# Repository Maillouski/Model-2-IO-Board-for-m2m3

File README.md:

# M2 IO Emulator Board

**English** | [Français](README.fr.md)

A drop-in replacement for the **Sega 837-10539 I/O board** of the **Daytona USA twin** cabinet (Sega Model 2), built around an
**Arduino Mega 2560**. It lets an emulator drive the original cabinet: controls, lamps, meters, the original drive board (force
feedback) and the original arcade monitor.

> **Status: prototype.** The design passes DRC and ERC, but no board has been built or tested yet. Read
> [Open points](#open-points) before you order.

**Version: V5.1** (2026-11-15). V5.1 adds a USB-A socket (J19) that carries only the cabinet's 5 V and ground (no data lines), for example to power a Raspberry Pi, and new silkscreen notes. V5 (kept under the tag [`v5`](https://github.com/Maillouski/Model-2-IO-Board-for-m2m3/tree/v5)) replaces the HDMI → VGA converter of V3 (CS5213, U4) with an **MS9292** (U9), adds a 3.3 V
regulator for it (U10), and adds two audio connectors (J17, J18). V3 added the [HDMI input](#hdmi-input), a stereo audio output
and a [composite sync](#composite-sync) that no longer depends on the polarity of H and V. The state before V5 (V3.2) is kept under the tag
[`v3.2`](https://github.com/Maillouski/Model-2-IO-Board-for-m2m3/tree/v3.2), V2 (screen jumper JP8) under the tag [`v2`](https://github.com/Maillouski/Model-2-IO-Board-for-m2m3/tree/v2), and V1,
the first board, ordered from JLCPCB on 2026-10-13, under the tag [`v1`](https://github.com/Maillouski/Model-2-IO-Board-for-m2m3/tree/v1).

## What it does

The idea is simple: pull the Sega I/O board out of the cabinet and put this one in its place. It has the same size, the same
mounting holes and the same connector names, so the original harness plugs straight in. Nothing gets cut or rewired.

Once it's in, the Arduino Mega becomes the bridge between the emulator and the cabinet. It reads the controls and drives
everything the original board used to drive:

- **Controls** — steering, accelerator, brake, shifter, coin, START, the VR view buttons, TEST and SERVICE.
- **Lamps, meters and relay** — switched by a ULN2803A, so the original bulbs and coin meters keep working.
- **Force feedback** — the original drive board stays in the cabinet and gets its commands from the Mega, so the wheel keeps
  its original force feedback.
- **Video** — an HDMI input (V3) or a VGA input goes to the original arcade monitor, with composite sync built on the board
  (negative, whatever the H/V polarity). A small switchable video amplifier lifts the signal to the level the tube expects.
- **Sound** — the audio carried by the HDMI input comes out on two RCA jacks (J16). A separate 3-pin input (J17) is passed straight
  through to a 4-pin output (J18) for the cabinet's preamp.
- **USB-A 5 V (J19)** — a USB-A socket wired to the cabinet's 5 V (+5V_BORNE) and ground only; D+ and D− are left unconnected, so it supplies power and no data. It is meant to power a small host such as a Raspberry Pi from the cabinet. Nothing protects it (no fuse). The silkscreen reminds you to set the cabinet's 5 V rail to 5.10 V.

A few practical details make bring-up easier: TEST and SERVICE buttons right on the board, a power LED, test points for each
supply, and a jumper (JP1) to choose whether the drive board logic runs from the Mega's 5 V or from the cabinet's.

## Video jumpers

| VIDEO IN (J13) | JP2-JP4 (VIDEO AMP) | JP5-JP7 (VGA TERM 75 Ω) |
|---|---|---|
| PC / HDMI-VGA adapter | ON | ON |
| Arcade RGB | OFF | OFF |

The same table is printed on the board. With the HDMI input, use the first row: U9 is the same kind of chip as the one inside an HDMI-to-VGA
adapter (V5.1 has not been built yet, see [Open points](#open-points)).

## Composite sync

U2 (74HCT86) builds the composite sync for the monitor from H and V, after the circuit of
[Tomi Engdahl](https://www.epanorama.net/circuits/vga2rgbs.html), pointed out by Zebidee on the ArcadeControls.com forum. Each sync is compared (XOR) with its own average, taken by an
RC filter (R66 + C47 for H, R67 + C48 for V: 2.2 kΩ, 22 µF), so its pulses always come out positive; the two are then combined
and inverted. The result is a **negative** composite sync whatever the polarity of H and V at the input, which is what the
original monitor expects. After a change of polarity (new video mode), the filters settle within a fraction of a second. It
goes to VIDEO OUT through R47 (470 Ω).

## HDMI input

J15 takes the host's HDMI output directly; U9 (Macrosilicon MS9292) turns it into analog R/G/B with H/V sync and stereo audio, so
no external HDMI → VGA adapter is needed. The VGA input J13 is still there, and a jumper chooses between the two. V3 used a CS5213
for this job; V5 uses the MS9292 because the CS5213 cannot be bought from regular distributors.

| Jumper | Setting | Effect |
|---|---|---|
| JP9 (VIDEO INPUT SOURCE) | ON | video from the HDMI input (J15, through U9) |
| JP9 | OFF | video from the VGA input (J13), as on V2 |
| JP10 (HDMI CHIP 5V SELECT) | 1-2 | U9 and its 3.3 V regulator run from the Mega's 5 V |
| JP10 | 2-3 | they run from the cabinet's 5 V, through a ferrite filter (FB1) |

- The switch is made by U7 (TS5V330, R/G/B) and U8 (74HCT157, H/V sync); everything after it (amplifier, composite sync, VIDEO
  OUT) is the same as on V2.
- **Power:** the MS9292 has no 5 V input pin. U10 (NCP1117ST33T3G) makes its 3.3 V from the 5 V of JP10; its 1.2 V comes from a
  buck converter inside the chip with L1 (10 µH power inductor, Bourns SRN4018-100M). Decoupling follows the maker's reference circuit (figure 3 of datasheet V1.5).
- **Video level:** the DAC outputs go to ground through R75-R77 (75 Ω), in parallel with the VGA termination R48-R50 (75 Ω, JP5-JP7), so
  the DAC sees 37.5 Ω. On an MS9292 evaluation board, 75 Ω alone made the video amplifier saturate.
- **Audio:** J16, a stacked RCA jack: **top = left**, **bottom = right**, fed by the chip's DAC through 470 Ω + 10 µF in series per
  channel. The footprint takes a Same Sky RCJ-2223 (DigiKey; red on top, so red = left) or a Lian Xin XDJK-0271-1650 (LCSC C7527522;
  white on top, red at the bottom). J17 (AUDIO input, 3-pin JST PH 2.00 mm: 1 left, 2 ground, 3 right) takes a straight cable from
  the host's line output and goes straight to J18 (AUDIO OUT, 4-pin JST NH 2.50 mm: 1 left, 2 ground, 3 right, 4 ground) for the
  cabinet's preamp. The two audio paths are separate: there is no selector.
- **Hot plug:** the chip drives the HPD line itself (its HDRXHPD output). The V3 pull-up R60 is not fitted.
- **EDID:** U6, an AT24C02 EEPROM on the HDMI DDC lines (address 0x50, decoupled by C24), is fitted and comes **blank**; U9's own
  DDC pins are not connected (R73 and R74, 0 Ω, are not fitted). The host must write a 256-byte EDID into it (the monitor's video mode, and HDMI audio if wanted):
  while it is blank, the host reads an invalid EDID. Its write protect is tied low, so it is programmed in place, through the
  HDMI cable.

## Screen jumper (JP8)

New in V2. JP8 ties the Mega's D36 pin to ground. The Mega reads it with its internal pull-up and sends it to the host with the
other inputs, so the host can choose its screen at start-up. Once the board is in the cabinet, switching screens only takes the
jumper, not a software change.

| JP8 | Screen |
|---|---|
| ON | CRT (4:3): the original arcade monitor, through the HDMI input (V3) or an HDMI-to-VGA adapter |
| OFF | LVDS panel (16:9) |

Printed on the board as SCREEN / ON = CRT (4:3) / OFF = LVDS 16:9. What the host does with this input is up to the host
software (see [Driving it from a computer](#driving-it-from-a-computer)).

## Driving it from a computer

The board comes with its Arduino Mega program ([`firmware/`](firmware/m2io-mega)) and a test console
([`tools/m2io_console.py`](tools/m2io_console.py)). To run Daytona USA on your own computer or emulator build and reach the
cabinet through this board, read **[Driving the board from your own host](docs/HOST-PROTOCOL.md)**: serial link, frames,
byte meanings, how to connect them to MAME's emulated I/O board, and the pitfalls to avoid.

## 3D views

Rendered with KiCad 10 from the files in this repository.

| | |
|---|---|
|  |  |
| Perspective view | Video section: VGA and HDMI inputs, source switch, OPA3355 amplifier, jumpers and settings tables |
|  |  |
| Top | Bottom |

## Repository

| Path | Contents |
|---|---|
| `kicad/` | KiCad 10 project: schematic, PCB, design rules, project footprint library (`interface-borne.pretty`), 3D models |
| `fabrication/` | Gerbers, Excellon drill files and drill maps (`gerbers/`), the same files zipped for the fab, pick-and-place file; JLCPCB BOM and CPL for SMD assembly ([`jlcpcb/`](fabrication/jlcpcb/README.md)) |
| `firmware/` | Arduino Mega program (`m2io-mega/`) and its PC test without a Mega (`test/`) |
| `tools/` | Test console: plays the host's part from any computer (Python 3 + pyserial) |
| `bom/` | Full BOM ([`BOM.md`](bom/BOM.md)) and DigiKey import file ([`BOM-digikey.csv`](bom/BOM-digikey.csv)) |
| `docs/` | [Host protocol](docs/HOST-PROTOCOL.md), schematic PDF, board renders |

Board: 2 layers, 180 × 190 mm. Gerbers come from the PCB's own plot settings (KiCad 10).

## Open points

- **V5.1 has not been built.** The MS9292 circuit follows the maker's reference design; the video levels were measured on an MS9292
  evaluation board, not on this board. Its behaviour with the 24 kHz mode of the arcade monitor on this board is not verified,
  and the HDMI pairs run on a 2-layer board without controlled impedance. V1 is the only board that has been ordered.
- **J19 (USB-A 5 V) is not verified under load.** The 5 V track that feeds it is 3 mm wide on most of its run, but the current it can deliver, the voltage drop and the need for a fuse have not been measured. The part is a Molex 67643-type USB-A socket (footprint and 3D model from the KiCad library); the exact part number is not confirmed, and it is not in the JLCPCB assembly files (solder it by hand).
- **U9's exposed pad is tied to ground**, which the datasheet does not state; check continuity (pad to pin 17) on the first chips. The pad
  has 9 vias: order "Epoxy Filled & Capped" vias or reduce the paste.
- **Fine vias and tracks:** the HDMI block uses 0.15 mm tracks and vias down to 0.45 / 0.20 mm (27 vias are 0.45 / 0.20 mm,
  right at the size JLCPCB surcharges); the rest of the board keeps 0.2 mm tracks and 0.6 / 0.3 mm vias. Confirm with the fabricator's quote.
- **CN1 and CN2** are plain 3M four-wall headers, without ejector latches.

## 3D models

The Arduino Mega model in `kicad/3d/` is derived from Arduino's CAD files (CC BY-SA 4.0) and KiCad library models; see
[`kicad/3d/README.md`](kicad/3d/README.md). The JST NH connectors and the RCA jack (J16, drawn as the RCJ-2223) use simplified models made for this project; U9, L1, U10 and J17 use the standard KiCad models.

## Credits

Sources used for this board: SEGA Daytona USA manuals; MAME (Dirk Best for the Model 1 I/O board; R. Belmont, O. Galibert,
ElSemi, A. Salese, M. Daniels for Model 2); M2Pac by BigPanik (Gamoover); DaytonaUSB by SailorSat; BackForceFeeder by njz3; MEGA
adapters by Tibal; the MiSTer project (video to arcade monitor); Tomi Engdahl (composite sync circuit); Zebidee on the ArcadeControls.com forum.

Not affiliated with or endorsed by SEGA.

## License

© 2026 Nicolas Mailloux. **CC BY-NC-SA 4.0** — see [`LICENSE`](LICENSE).
You may build, use, modify and share this board, as long as you credit the author, keep the credits, and share changes under the
same license. **No commercial use**: don't sell the board, the files or a derivative.
The firmware and the tools are under the same license.

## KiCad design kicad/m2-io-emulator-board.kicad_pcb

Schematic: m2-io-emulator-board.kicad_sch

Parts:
C1, C2, C3, C4, C5, C6, C7, C8, C9, C10, C11, C12, C13, C14, C15, C16, C18, C20, C21, C22, C24, C33, C43, C44, C46: 100 nF; C_0805_2012Metric; MPN CC0805KRX7R9BB104
C17: 100 µF 16 V; CP_Radial_D6.3mm_P2.50mm; MPN EEU-FC1C101H
C19, C23, C25, C32, C41, C42, C45, C49, C51, C52, C53: 10 µF; C_0805_2012Metric; MPN CL21A106KAYNNNE
C39, C40: 10 nF; C_0805_2012Metric; MPN CC0805KRX7R9BB103
C47, C48: 22 µF; C_0805_2012Metric; MPN CL21A226MOCLRNC
C50: 100 nF; C_0805_2012Metric; MPN CC0805KRX7R9BB104; not fitted
D1: LED verte 3 mm; LED_D3.0mm; MPN_CMS_Flux LTST-C170KGKT
FB1: 600 Ω @ 100 MHz; L_0805_2012Metric; MPN GZ2012D601TF
J1: N2550-6002-RB; IDC-Header_2x25_P2.54mm_Vertical; MPN N2550-6002-RB
J2: N2526-6002-RB; IDC-Header_2x13_P2.54mm_Vertical; MPN N2526-6002-RB
J3: B10P-SHF-1AA; JST_NH_B10P-SHF-1AA_1x10_P2.50mm_Vertical; MPN B10P-SHF-1AA
J4, J5: B12P-SHF-1AA; JST_NH_B12P-SHF-1AA_1x12_P2.50mm_Vertical; MPN B12P-SHF-1AA
J6, J7, J8, J9, J10: 61300811121; PinHeader_1x08_P2.54mm_Vertical; MPN 61300811121
J11: 61301011121; PinHeader_1x10_P2.54mm_Vertical; MPN 61301011121
J12: Pin Header 02x18 2.54mm Vertical; PinHeader_2x18_P2.54mm_Vertical; MPN Pin Header 02x18 2.54mm Vertical
J13: VGA femelle; DSUB-15-HD_Socket_Horizontal_P2.29x2.54mm_EdgePinOffset8.35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; MPN L77HDE15SD1CH4F
J14: VIDEO; JST_NH_B5P-SHF-1AA_1x05_P2.50mm_Vertical; MPN B5P-SHF-1AA
J15: HDMI A; HDMI_A_Amphenol_10029449-x01xLF_Horizontal; MPN 10029449-111RLF
J16: XDJK-0271-1650; RCA_Dual_Stacked_RCJ-22xx_XDJK-0271-1650; MPN XDJK-0271-1650
J17: AUDIO M3; JST_PH_B3B-PH-K_1x03_P2.00mm_Vertical; MPN B3B-PH-K-S
J18: AUDIO OUT; JST_NH_B4P-SHF-1AA_1x04_P2.50mm_Vertical; MPN B4P-SHF-1AA
J19: USB-A 5V BORNE; USB_A_Molex_67643_Horizontal; MPN Molex 67643-3910
JP1, JP2, JP3, JP4, JP10: 61300311121; PinHeader_1x03_P2.54mm_Vertical; MPN 61300311121
JP5, JP6, JP7, JP8, JP9: 61300211121; PinHeader_1x02_P2.54mm_Vertical; MPN 61300211121
L1: 10 µH 0,7 A; L_Bourns-SRN4018; MPN SRN4018-100M
R1, R2, R3, R4, R5, R6, R7, R8, R9, R10, R11, R12, R13: 4,7 kΩ; R_0805_2012Metric; MPN RC0805FR-074K7L
R14, R15, R16, R17, R18, R19, R20, R21, R22, R23, R24, R25, R26, R27, R28, R29, R30, R31, R32, R33, R34, R35, R36, R37, R46: 1 kΩ; R_0805_2012Metric; MPN RC0805FR-071KL
R38, R39, R40, R41, R42, R43, R44, R45, R61, R62, R63, R64, R65, R68, R70: 10 kΩ; R_0805_2012Metric; MPN RC0805FR-0710KL
R47, R71, R72: 470 Ω; R_0805_2012Metric; MPN RMCF0805FT470R
R48, R49, R50, R75, R76, R77: 75 Ω; R_0805_2012Metric; MPN RC0805FR-0775RL
R51, R52, R53: 604 Ω; R_0805_2012Metric; MPN RC0805FR-07604RL
R54, R55, R56: 200 Ω; R_0805_2012Metric; MPN RC0805FR-07200RL
R57, R58, R59: 33 Ω; R_0805_2012Metric; MPN RC0805FR-0733RL
R60: 1 kΩ; R_0805_2012Metric; MPN RC0805FR-071KL; not fitted
R66, R67: 2,2 kΩ; R_0805_2012Metric; MPN RC0805FR-072K2L
R69: 560 Ω; R_0805_2012Metric; MPN RC0805FR-07560RL
R73, R74: 0 Ω; R_0805_2012Metric; MPN RC0805JR-070RL; not fitted
SH1, SH2, SH3, SH4, SH5, SH6, SH7, SH8, SH9, SH10: 382811-8; MPN 382811-8
SW1: TEST; SW_PUSH_6mm; MPN 1825910-6
SW2: SERVICE; SW_PUSH_6mm; MPN 1825910-6
TP1, TP2, TP3, TP4: 5002; TestPoint_Keystone_5000-5004_Miniature; MPN 5002; not fitted
U1: ULN2803A; DIP-18_W7.62mm; MPN ULN2803A
U2: 74HCT86; SOIC-14_3.9x8.7mm_P1.27mm; MPN 74HCT86D,653
U3: OPA3355EA; TSSOP-14_4.4x5mm_P0.65mm; MPN OPA3355EA/2K5
U6: AT24C02; SOIC-8_3.9x4.9mm_P1.27mm; MPN AT24C02C-SSHM-T
U7: TS5V330; TSSOP-16_4.4x5mm_P0.65mm; MPN TS5V330CPWR
U8: 74HCT157; SOIC-16_3.9x9.9mm_P1.27mm; MPN SN74HCT157DR
U9: MS9292; QFN-48-1EP_6x6mm_P0.4mm_EP4.2x4.2mm_ThermalVias_D0.3; MPN MS9292
U10: LDO 3.3 V; SOT-223-3_TabPin2; MPN NCP1117ST33T3G

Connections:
/+1V2: C53.1, L1.2, U9.3 (AVDD12), U9.9 (AVDD12), U9.37 (DVDD12), U9.40 (FB)
/+3V3: C51.1, C52.1, R70.2, U9.6 (AVDD33), U9.16 (DVDD33), U9.20 (VREFH), U9.34 (AVDD33), U9.42 (V33IN), U9.47 (AVDD33), U10.2 (OUT)
/+5V_BORNE: C17.1, C18.1, FB1.1, J1.34, J1.36, J1.38, J1.50, J3.1, J3.2, J3.3, J3.4, J19.1 (VBUS), JP1.3, R46.1, TP2.1 (1_1), U1.10 (COMMON_FREE__WHEELING_DIODES)
/+5V_BORNE_F: C45.1, C46.1, FB1.2, JP10.3
/+5V_CONV: C25.1, C32.1, C33.1, JP10.2, U10.3 (IN)
/+5V_MEGA: C19.1, C20.1, C21.1, C22.1, C23.1, C43.1, C44.1, J2.1, J2.7, J6.5, J12.1 (Pin_2), J12.2 (Pin_1), JP1.1, JP10.1, R1.1, R2.1, R3.1, R4.1, R5.1, R6.1, R7.1, R8.1, R9.1, R10.1, R11.1, R12.1, R13.1, R38.1, R39.1, R40.1, R41.1, R42.1, R43.1, R44.1, R45.1, R61.2, TP3.1 (1_1), U2.10 (3B), U2.14 (VCC), U3.1 (ENA), U3.2 (ENB), U3.3 (ENC), U3.4 (V+), U7.16 (VCC), U8.16 (VCC)
/AMP_B: JP4.1, R59.2
/AMP_FB_B: R53.2, R56.1, U3.13 (-INC)
/AMP_FB_G: R52.2, R55.1, U3.9 (-INB)
/AMP_FB_R: R51.2, R54.1, U3.6 (-INA)
/AMP_G: JP3.1, R58.2
/AMP_OUT_B: R53.1, R59.1, U3.14 (OUTC)
/AMP_OUT_G: R52.1, R58.1, U3.8 (OUTB)
/AMP_OUT_R: R51.1, R57.1, U3.7 (OUTA)
/AMP_R: JP2.1, R57.2
/AN_ACCEL: J2.4, R28.1
/AN_BRAKE: J2.9, R29.1
/AN_STEER: J2.3, R27.1
/AUDIO_M3_L: J17.1 (L), J18.1 (L)
/AUDIO_M3_R: J17.3 (R), J18.3 (R)
/AUD_OUT_L: C41.2, J16.3 (X1_HAUT)
/AUD_OUT_R: C42.2, J16.2 (X2_BAS)
/CSYNC_N: R47.1, U2.8 (3Y)
/CSYNC_XOR: U2.9 (3A), U2.11 (4Y)
/DRV_I0: J4.2, R30.1
/DRV_I1: J4.3, R31.1
/DRV_I2: J4.4, R32.1
/DRV_I3: J4.5, R33.1
/DRV_I4: J4.7, R34.1
/DRV_I5: J4.8, R35.1
/DRV_I6: J4.9, R36.1
/DRV_I7: J4.10, R37.1
/DRV_O0: J5.2, J12.4 (Pin_3)
/DRV_O1: J5.3, J12.3 (Pin_4)
/DRV_O2: J5.4, J12.6 (Pin_5)
/DRV_O3: J5.5, J12.5 (Pin_6)
/DRV_O4: J5.7, J12.8 (Pin_7)
/DRV_O5: J5.8, J12.7 (Pin_8)
/DRV_O6: J5.9, J12.10 (Pin_9)
/DRV_O7: J5.10, J12.9 (Pin_10)
/GND: C1.2, C2.2, C3.2, C4.2, C5.2, C6.2, C7.2, C8.2, C9.2, C10.2, C11.2, C12.2, C13.2, C14.2, C15.2, C16.2, C17.2, C18.2, C19.2, C20.2, C21.2, C22.2, C23.2, C24.2, C25.2, C32.2, C33.2, C39.2, C40.2, C43.2, C44.2, C45.2, C46.2, C47.2, C48.2, C49.2, C50.2, C51.2, C52.2, C53.2, D1.1 (K), J1.2, J1.4, J1.6, J1.10, J1.26, J2.6, J2.11, J3.7, J3.8, J3.9, J3.10, J4.12, J6.6, J6.7, J11.4, J12.35 (Pin_36), J12.36 (Pin_35), J13.5 (GND), J13.6 (R_GND), J13.7 (V_GND), J13.8 (B_GND), J13.10 (SYNC_GND), J13.SH (BLINDAGE), J14.5 (GND), J15.2 (D2S), J15.5 (D1S), J15.8 (D0S), J15.11 (CKS), J15.17 (GND), J15.SH (SHIELD), J16.1 (BARREL), J17.2 (GND), J18.2 (GND), J18.4 (GND), J19.4 (GND), J19.SH (SHIELD), JP5.2, JP6.2, JP7.2, JP8.2, JP9.2, R54.2, R55.2, R56.2, R62.2, R63.2, R64.2, R65.2, R68.2, R69.2, R75.2, R76.2, R77.2, SW1.2, SW2.2, TP1.1 (1_1), U1.9 (GND), U2.7 (GND), U3.11 (V-), U6.1 (A0), U6.2 (A1), U6.3 (A2), U6.4 (GND), U6.7 (WP), U7.8 (GND), U7.12 (DD), U7.13 (S2D), U7.14 (S1D), U7.15 (~EN), U8.8 (GND), U8.10 (3B), U8.11 (3A), U8.13 (4B), U8.14 (4A), U8.15 (~G), U9.17 (VSS), U9.19 (VREFL), U9.30 (VSS), U9.38 (VSS), U9.39 (VSS), U9.49 (EPAD), U10.1 (GND)
/HDMI_5V: C24.1, J15.18 (+5V), R60.2, U6.8 (VCC), U9.44 (HDRXDET)
/HDMI_CK_N: J15.12 (CK-), U9.1 (HDRXCN)
/HDMI_CK_P: J15.10 (CK+), U9.2 (HDRXCP)
/HDMI_D0_N: J15.9 (D0-), U9.4 (HDRX0N)
/HDMI_D0_P: J15.7 (D0+), U9.5 (HDRX0P)
/HDMI_D1_N: J15.6 (D1-), U9.7 (HDRX1N)
/HDMI_D1_P: J15.4 (D1+), U9.8 (HDRX1P)
/HDMI_D2_N: J15.3 (D2-), U9.10 (HDRX2N)
/HDMI_D2_P: J15.1 (D2+), U9.11 (HDRX2P)
/HDMI_HPD: J15.19 (HPD), R60.1, U9.43 (HDRXHPD)
/HDMI_SCL: J15.15 (SCL), R74.2, U6.6 (SCL)
/HDMI_SDA: J15.16 (SDA), R73.2, U6.5 (SDA)
/HD_AUD_L: C39.1, C41.1, R71.2
/HD_AUD_R: C40.1, C42.1, R72.2
/HD_B: R77.1, U7.11 (S1C), U9.31 (BOUT)
/HD_G: R76.1, U7.5 (S1B), U9.32 (GOUT)
/HD_HS: R62.1, U8.2 (1A), U9.23 (HSOUT)
/HD_R: R75.1, U7.2 (S1A), U9.33 (ROUT)
/HD_VS: R63.1, U8.5 (2A), U9.24 (VSOUT)
/HS_AVG: C47.1, R66.2, U2.2 (1B)
/HS_NORM: U2.3 (1Y), U2.13 (4B)
/IN_COIN1: C1.1, J1.1, R1.2, R14.1
/IN_COIN2: C2.1, J1.3, R2.2, R15.1
/IN_SERVICE: C4.1, J1.7, R4.2, R17.1, SW2.1
/IN_SH13: C10.1, J1.25, R10.2, R23.1
/IN_SH24: C11.1, J1.27, R11.2, R24.1
/IN_SH1234: C12.1, J1.29, R12.2, R25.1
/IN_SH_NU: C13.1, J1.31, R13.2, R26.1
/IN_START: C5.1, J1.9, R5.2, R18.1
/IN_TEST: C3.1, J1.5, R3.2, R16.1, SW1.1
/IN_VR1: C6.1, J1.11, R6.2, R19.1
/IN_VR2: C7.1, J1.13, R7.2, R20.1
/IN_VR3: C8.1, J1.15, R8.2, R21.1
/IN_VR4: C9.1, J1.17, R9.2, R22.1
/J13_B: J13.3 (B), U7.10 (S2C)
/J13_G: J13.2 (V), U7.6 (S2B)
/J13_HS: J13.13 (HSYNC), R64.1, U8.3 (1B)
/J13_R: J13.1 (R), U7.3 (S2A)
/J13_VS: J13.14 (VSYNC), R65.1, U8.6 (2B)
/LED_BORNE_A: D1.2 (A), R46.2
/MEGA_A0_STEER: C14.1, J7.1, R27.2
/MEGA_A1_ACCEL: C15.1, J7.2, R28.2
/MEGA_A2_BRAKE: C16.1, J7.3, R29.2
/MEGA_A8_METER1: J8.1, U1.1 (IN_1)
/MEGA_A9_METER2: J8.2, U1.2 (IN_2)
/MEGA_A10_LAMP_START: J8.3, U1.3 (IN_3)
/MEGA_A11_LAMP_VR1: J8.4, U1.4 (IN_4)
/MEGA_A12_LAMP_VR2: J8.5, U1.5 (IN_5)
/MEGA_A13_LAMP_VR3: J8.6, U1.6 (IN_6)
/MEGA_A14_LAMP_VR4: J8.7, U1.7 (IN_7)
/MEGA_A15_LEADER: J8.8, U1.8 (IN_8)
/MEGA_D10_DRV_I4: J11.8, R34.2, R42.2
/MEGA_D11_DRV_I5: J11.7, R35.2, R43.2
/MEGA_D12_DRV_I6: J11.6, R36.2, R44.2
/MEGA_D13_DRV_I7: J11.5, R37.2, R45.2
/MEGA_D30_SH_NU: J12.12 (Pin_11), R26.2
/MEGA_D31_SH1234: J12.11 (Pin_12), R25.2
/MEGA_D32_SH24: J12.14 (Pin_13), R24.2
/MEGA_D33_SH13: J12.13 (Pin_14), R23.2
/MEGA_D36_ECRAN: J12.18 (Pin_17), JP8.1
/MEGA_D37_VR4: J12.17 (Pin_18), R22.2
/MEGA_D42_VR3: J12.24 (Pin_23), R21.2
/MEGA_D43_VR2: J12.23 (Pin_24), R20.2
/MEGA_D44_VR1: J12.26 (Pin_25), R19.2
/MEGA_D45_START: J12.25 (Pin_26), R18.2
/MEGA_D46_SERVICE: J12.28 (Pin_27), R17.2
/MEGA_D47_TEST: J12.27 (Pin_28), R16.2
/MEGA_D48_COIN2: J12.30 (Pin_29), R15.2
/MEGA_D49_COIN1: J12.29 (Pin_30), R14.2
/MEGA_D50_DRV_I3: J12.32 (Pin_31), R33.2, R41.2
/MEGA_D51_DRV_I2: J12.31 (Pin_32), R32.2, R40.2
/MEGA_D52_DRV_I1: J12.34 (Pin_33), R31.2, R39.2
/MEGA_D53_DRV_I0: J12.33 (Pin_34), R30.2, R38.2
/MS_AUD_L: R71.1, U9.21 (ALOUT)
/MS_AUD_R: R72.1, U9.18 (AROUT)
/MS_DACREF: R69.1, U9.29 (DACREF)
/MS_REXT: R68.1, U9.48 (REXT)
/MS_RSTN: C50.1, R70.1, U9.15 (RSTN)
/MS_RXSCL: R74.1, U9.46 (RXDDCSCL)
/MS_RXSDA: R73.1, U9.45 (RXDDCSDA)
/MS_V12SW: L1.1, U9.41 (V12OUT)
/MS_VMID: C49.1, U9.25 (VMID)
/OUT_LAMP_START: J1.37, U1.16 (OUT_3)
/OUT_LAMP_VR1: J1.39, U1.15 (OUT_4)
/OUT_LAMP_VR2: J1.41, U1.14 (OUT_5)
/OUT_LAMP_VR3: J1.43, U1.13 (OUT_6)
/OUT_LAMP_VR4: J1.45, U1.12 (OUT_7)
/OUT_LEADER: J1.47, U1.11 (OUT_8)
/OUT_METER1: J1.33, U1.18 (OUT_1)
/OUT_METER2: J1.35, U1.17 (OUT_2)
/SRC_SEL: JP9.1, R61.1, U7.1 (IN), U8.1 (~A/B)
/TERM_B: JP7.1, R50.2
/TERM_G: JP6.1, R49.2
/TERM_R: JP5.1, R48.2
/VCC_DRIVE: J1.42, J1.44, JP1.2, TP4.1 (1_1)
/VGA_B: JP4.3, R50.1, U3.12 (+INC), U7.9 (DC)
/VGA_G: JP3.3, R49.1, U3.10 (+INB), U7.7 (DB)
/VGA_HS: R66.1, U2.1 (1A), U8.4 (1Y)
/VGA_R: JP2.3, R48.1, U3.5 (+INA), U7.4 (DA)
/VGA_VS: R67.1, U2.5 (2B), U8.7 (2Y)
/VIDEO_SYNC: J14.4 (SYNC), R47.2
/VID_B: J14.3 (B), JP4.2
/VID_G: J14.2 (V), JP3.2
/VID_R: J14.1 (R), JP2.2
/VS_AVG: C48.1, R67.2, U2.4 (2A)
/VS_NORM: U2.6 (2Y), U2.12 (4A)

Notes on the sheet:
Boutons de la carte (2026-10-09) : SW1 = TEST, SW2 = SERVICE (comme SW6 et SW7 de la carte E/S d'origine), vers la masse ; anti-rebond par le conditionneur de l'entrée (4,7 kΩ / 100 nF / 1 kΩ).
Ampli vidéo R/V/B (2026-10-12) : U3 OPA3355, gain 4,02 (RF 604 Ω / RG 200 Ω), RS 33 Ω en sortie ; +5V_MEGA. JP2-JP4 (R, V, B) : 1-2 = AMP, 2-3 = DIR (VGA direct vers J14). JP5-JP7 : terminaison 75 Ω (R48-R50) en service si posé. Adaptateur HDMI → VGA (0,7 V) : AMP + JP5-JP7 posés. Source déjà au ni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
Choix de l'écran de l'hôte (2026-10-13, carte V2) : JP8 relie D36 du Mega (bit 1 de IN1, rappel interne) à la masse. Cavalier posé = HDMI vers le tube (24 kHz, 4:3) ; retiré = LVDS (16:9). Lu par l'hôte au démarrage, par le Mega.
V3 (2026-10-15, non publiée) : HDMI → VGA intégré. J15 HDMI → U4 CS5213 OU U5 NX3303X (jamais les deux) → U7/U8. JP9 SOURCE : posé = HDMI, retiré = VGA J13 (comme la V2). Sorties = VGA_R/G/B/HS/VS (U2, U3, JP2-JP4 inchangés). JP10 alim de la puce : 1-2 = +5V_MEGA, 2-3 = +5V_BORNE filtré (FB1). U6 E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
Bloc vidéo tube (2026-10-07) : VGA de l'adaptateur HDMI → VGA → synchro composite (74HCT86) → fiche vidéo du faisceau (J14). J14 « VIDEO » : ordre de la NH5P de la carte filtre 839-0683 (1 R, 2 V, 3 B, 4 SYNC, 5 GND). R48-R50 (75 Ω) posées depuis le 2026-10-12, en service par JP5-JP7 ; J14 R/V/B pa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
V3 (2026-10-16) : synchro indépendante de la polarité (T. Engdahl). U2 portes 1-2 : chaque synchro XOR sa moyenne (2,2 kΩ / 22 µF) → HS_NORM, VS_NORM en impulsions positives → porte 4 → porte 3 (inversion) : CSYNC négative quelles que soient les polarités H/V.

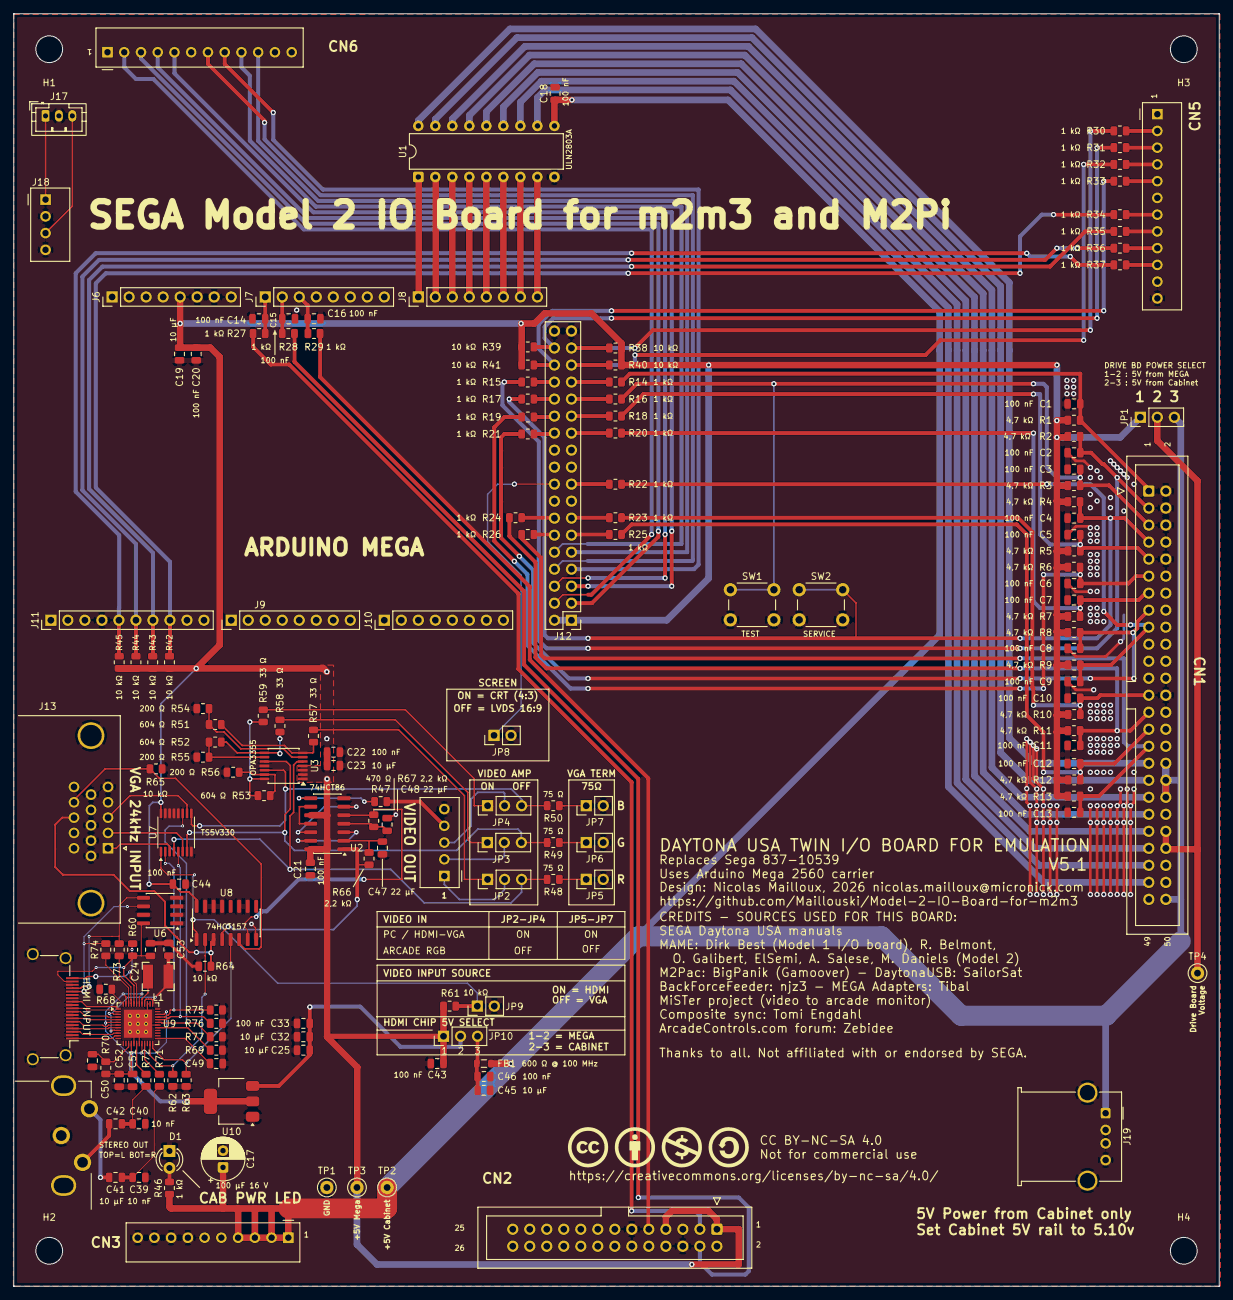
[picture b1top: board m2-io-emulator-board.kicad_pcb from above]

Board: 2 copper layers, 180.0 x 190.0 mm, 171 parts (0 on the bottom side), 147 nets.

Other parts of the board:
H1, H2, H3, H4: MountingHole_4.0mm
LOGO1: CC_BY-NC-SA_4.0
MEGA1: Arduino Mega 2560 (à l'envers); Arduino_Mega2560_3D

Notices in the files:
parts and their libraries:
Pictogrammes Creative Commons CC BY NC SA (icônes officielles, mirrors.creativecommons.org/presskit/icons) et mention de la licence CC BY-NC-SA 4.0, sérigraphie
https://creativecommons.org/licenses/by-nc-sa/4.0
